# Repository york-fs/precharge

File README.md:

# Precharge Board

The precharge board is responsible for precharging the inverter's large capacitance through a dedicated relay and
resistor before the AIRs close.

[Latest Release](https://github.com/york-fs/precharge/releases/latest)
[Interactive BOM](https://york-fs.github.io/precharge/ibom.html)

## Features

* **CAN Communication**
* **AIR Relay Control**
* **HV Sampling of Accumulator and TS sides**

## Cloning

A recursive clone must be used to download the `kicad-library` repository:

    git clone --recursive https://github.com/york-fs/precharge.git

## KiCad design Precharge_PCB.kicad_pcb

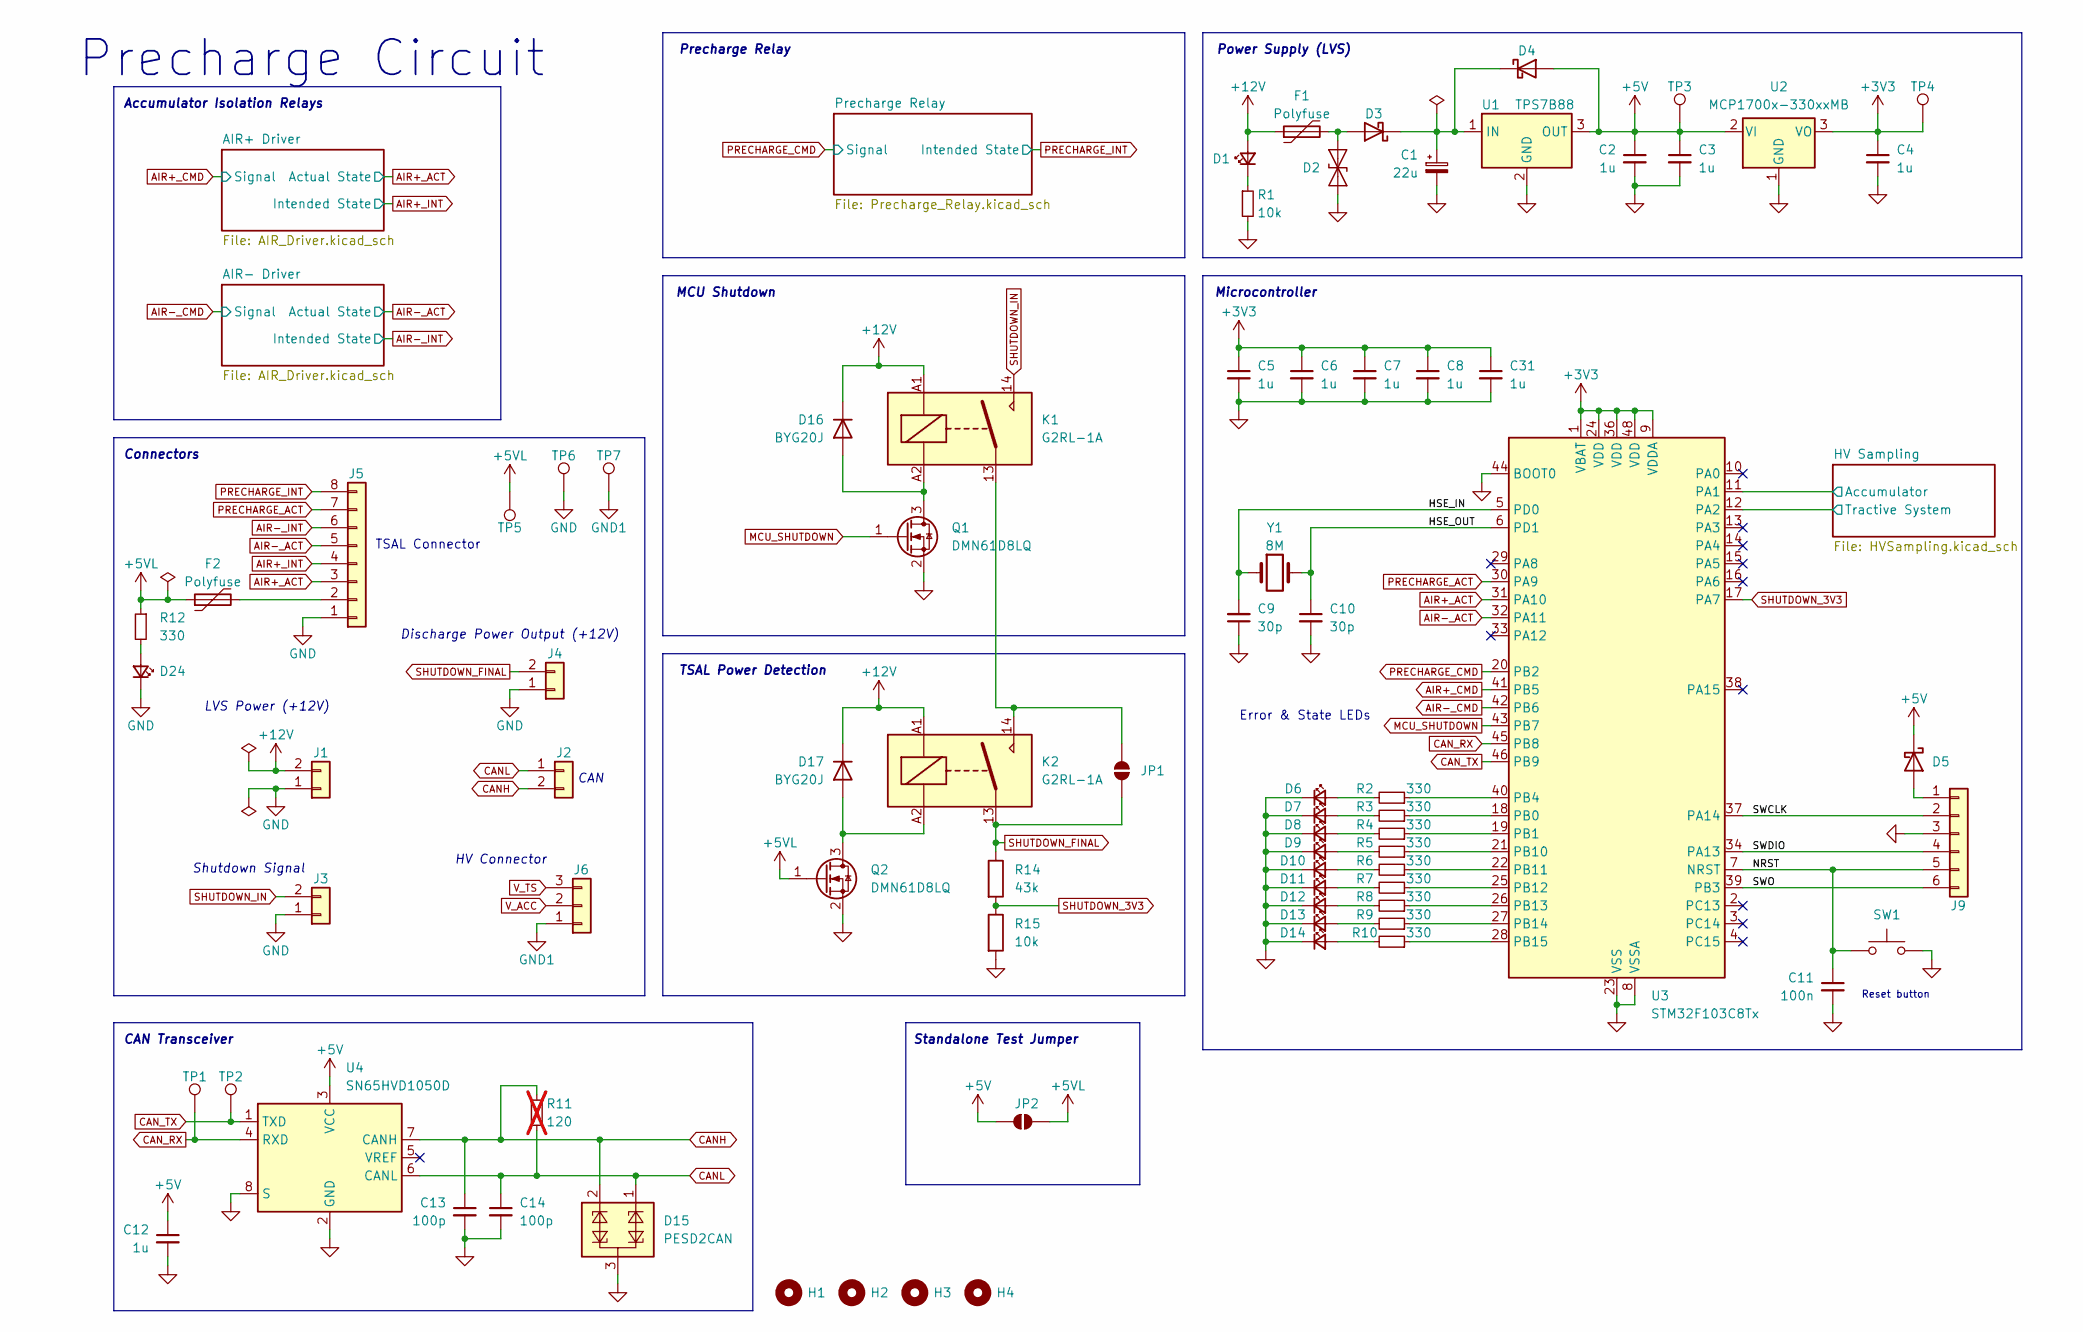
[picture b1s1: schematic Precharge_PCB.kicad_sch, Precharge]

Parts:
C1: 22u; CP_Elec_6.3x7.7; Mfr # EEEFK1J220XP; DigiKey # PCE3821CT-ND
C2, C3, C4, C5, C6, C7, C8, C12, C31: 1u; C_0603_1608Metric; Mfr # CL10B105KB8NQNC; LCSC # C5199872
C9, C10: 30p; C_0603_1608Metric; Mfr # GQM1875C2E300GB12D; DigiKey # 490-GQM1875C2E300GB12DCT-ND
C11: 100n; C_0603_1608Metric; Mfr # CL10B104KB8NNNC; DigiKey # 1276-1000-1-ND
C13, C14: 100p; C_0603_1608Metric; Mfr # GCM1885C2A101JA16D; DigiKey # 490-4771-1-ND
D1, D6, D7, D8, D9, D10, D11, D12, D13, D14, D24: LED_Small; LED_0603_1608Metric; Mfr # NCD0603R1; LCSC # C84263
D2: SMAJ24CA; D_SMA; Mfr # SMAJ24CA; DigiKey # SMAJ24CALFCT-ND
D3, D4, D5: D_Schottky; D_SOD-323; Mfr # NSR0530H; DigiKey # NSR0530HT1GOSCT-ND
D15: PESD2CAN; SOT-23; Mfr # PESD2CAN,215; DigiKey # 1727-3891-1-ND
D16, D17: BYG20J; D_SMA; Mfr # BYG20J-E3/TR; DigiKey # BYG20J-E3/TR3GICT-ND
F1, F2: Polyfuse; C_0805_2012Metric; Mfr # 0805L010/24YR; DigiKey # F11311CT-ND
H1, H2, H3, H4: MountingHole; MountingHole_3.2mm_M3
J1: Conn_01x02; MolexMicrofitPlus1x2; Mfr # 2157601022; DigiKey # 900-2157601022-ND
J2, J4: Conn_01x02; MolexMicrofitPlus1x2; Mfr # 2157601002; DigiKey # 900-2157601002-ND
J3: Conn_01x02; MolexMicrofitPlus1x2; Mfr # 2157601032; DigiKey # 900-2157601032-ND
J5: Conn_01x08; MolexMicrofitPlus1x8; Mfr # 2157601008; DigiKey # 900-2157601008-ND
J6: Conn_01x03; MolexMicrofitPlus1x3; Mfr # 2157601043; DigiKey # 900-2157601043-ND
J9: Conn_01x06; IDC-Connector-2x3; Mfr # HX JN1.27-2x3P ZZ H4.9; LCSC # C42372545
JP1, JP2: SolderJumper_2_Open; SolderJumper-2_P1.3mm_Open_TrianglePad1.0x1.5mm
K1, K2: G2RL-1A; Relay_SPST_Omron_G2RL-1A; Mfr # G2RL-1A-DC12; DigiKey # Z140-ND
Q1, Q2: DMN61D8LQ; SOT-23; Mfr # DMN61D8LQ-7; DigiKey # DMN61D8LQ-7DICT-ND
R1, R15: 10k; R_0603_1608Metric; Mfr # 0603WAF1002T5E; LCSC # C25804
R2, R3, R4, R5, R6, R7, R8, R9, R10, R12: 330; R_0603_1608Metric; Mfr # 0603WAF3300T5E; LCSC # C23138
R11: 120; R_0603_1608Metric; not fitted
R14: 43k; R_0603_1608Metric
SW1: SW_Push; SW_Push_1P1T_NO_Vertical_Wuerth_434133025816; Mfr # SKRPACE010; DigiKey # 4809-SKRPACE010CT-ND
TP1, TP2, TP3, TP4, TP5, TP6, TP7: TestPoint; TestPoint_Keystone_5000-5004_Miniature; Mouser # 534-5000; DigiKey # 36-5000-ND
U1: TPS7B88; TO-252-2; Mfr # TPS7B8850QKVURQ1; DigiKey # 296-TPS7B8850QKVURQ1CT-ND
U2: MCP1700x-330xxMB; SOT-89-3; Mfr # MCP1700T-3302E/MB; DigiKey # MCP1700T3302EMBCT-ND
U3: STM32F103C8Tx; LQFP-48_7x7mm_P0.5mm; Mfr # STM32F103C8T6; DigiKey # 497-17666-1-ND
U4: SN65HVD1050D; SOIC-8_3.9x4.9mm_P1.27mm; Mfr # SN65HVD1050DR; DigiKey # 296-26335-1-ND
Y1: 8M; Crystal_SMD_5032-2Pin_5.0x3.2mm; Mfr # X50328MSB2GI; LCSC # C115962

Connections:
+3V3: C4.1, C5.1, C6.1, C7.1, C8.1, C31.1, TP4.1, U2.3 (VO), U3.1 (VBAT), U3.9 (VDDA), U3.24 (VDD), U3.36 (VDD), U3.48 (VDD); also elsewhere on the board
+5V: C2.1, C3.1, C12.1, D4.2 (A), D5.1 (K), JP2.2 (B), TP3.1, U1.3 (OUT), U2.2 (VI), U4.3 (VCC)
+5VL: F2.1, JP2.1 (A), Q2.1 (G), R12.1, TP5.1; also elsewhere on the board
+12V: D1.2 (A), D16.1 (K), D17.1 (K), F1.1, J1.2, K1.A1, K2.A1
/HSE_IN: C9.2, U3.5 (PD0), Y1.1
/HSE_OUT: C10.1, U3.6 (PD1), Y1.2
/HV Sampling/Accumulator: U3.11 (PA1); also elsewhere on the board
/HV Sampling/Tractive System: U3.12 (PA2); also elsewhere on the board
/NRST: C11.1, J9.5, SW1.1, U3.7 (NRST)
/SWCLK: J9.2, U3.37 (PA14)
/SWDIO: J9.4, U3.34 (PA13)
/SWO: J9.6, U3.39 (PB3)
AIR+_ACT: J5.3, U3.31 (PA10); also elsewhere on the board
AIR+_CMD: U3.41 (PB5); also elsewhere on the board
AIR+_INT: J5.4; also elsewhere on the board
AIR-_ACT: J5.5, U3.32 (PA11); also elsewhere on the board
AIR-_CMD: U3.42 (PB6); also elsewhere on the board
AIR-_INT: J5.6; also elsewhere on the board
CANH: C13.1, D15.2 (C2), J2.2, R11.1, U4.7 (CANH)
CANL: C14.1, D15.1 (C1), J2.1, R11.2, U4.6 (CANL)
CAN_RX: TP1.1, U3.45 (PB8), U4.4 (RXD)
CAN_TX: TP2.1, U3.46 (PB9), U4.1 (TXD)
GND: C1.2, C2.2, C3.2, C4.2, C5.2, C6.2, C7.2, C8.2, C9.1, C10.2, C11.2, C12.2, C13.2, C14.2, C31.2, D2.1 (A1), D6.1 (K), D7.1 (K), D8.1 (K), D9.1 (K), D10.1 (K), D11.1 (K), D12.1 (K), D13.1 (K), D14.1 (K), D15.3 (CC), D24.1 (K), J1.1, J3.1, J4.1, J5.1, J9.3, Q1.2 (S), Q2.2 (S), R1.2, R15.2, SW1.2, TP6.1, U1.2 (GND), U2.1 (GND), U3.8 (VSSA), U3.23 (VSS), U3.35 (VSS), U3.44 (BOOT0), U3.47 (VSS), U4.2 (GND), U4.8 (S); also elsewhere on the board
GND1: J6.1, TP7.1; also elsewhere on the board
MCU_SHUTDOWN: Q1.1 (G), U3.43 (PB7)
unnamed: D1.1 (K), R1.1
unnamed: D2.2 (A2), D3.2 (A), F1.2
unnamed: C1.1, D3.1 (K), D4.1 (K), U1.1 (IN)
unnamed: D5.2 (A), J9.1
unnamed: D6.2 (A), R2.2
unnamed: D7.2 (A), R3.2
unnamed: D8.2 (A), R4.2
unnamed: D9.2 (A), R5.2
unnamed: D10.2 (A), R6.2
unnamed: D11.2 (A), R7.2
unnamed: D12.2 (A), R8.2
unnamed: D13.2 (A), R9.2
unnamed: D14.2 (A), R10.2
unnamed: D16.2 (A), K1.A2, Q1.3 (D)
unnamed: D17.2 (A), K2.A2, Q2.3 (D)
unnamed: D24.2 (A), R12.2
unnamed: F2.2, J5.2
unnamed: JP1.2 (B), K1.13, K2.14
unnamed: R3.1, U3.18 (PB0)
unnamed: R4.1, U3.19 (PB1)
unnamed: R2.1, U3.40 (PB4)
unnamed: R5.1, U3.21 (PB10)
unnamed: R6.1, U3.22 (PB11)
unnamed: R7.1, U3.25 (PB12)
unnamed: R8.1, U3.26 (PB13)
unnamed: R9.1, U3.27 (PB14)
unnamed: R10.1, U3.28 (PB15)
PRECHARGE_ACT: J5.7, U3.30 (PA9); also elsewhere on the board
PRECHARGE_CMD: U3.20 (PB2); also elsewhere on the board
PRECHARGE_INT: J5.8; also elsewhere on the board
SHUTDOWN_3V3: R14.2, R15.1, U3.17 (PA7)
SHUTDOWN_FINAL: J4.2, JP1.1 (A), K2.13, R14.1; also elsewhere on the board
SHUTDOWN_IN: J3.2, K1.14
V_ACC: J6.2; also elsewhere on the board
V_TS: J6.3; also elsewhere on the board

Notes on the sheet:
Microcontroller
Error & State LEDs
Connectors
Accumulator Isolation Relays
Standalone Test Jumper
TSAL Power Detection
CAN Transceiver
HV Connector
Power Supply (LVS)
Shutdown Signal
TSAL Connector
Precharge Relay
CAN
Discharge Power Output (+12V)
LVS Power (+12V)
Reset button
MCU Shutdown
Precharge Circuit

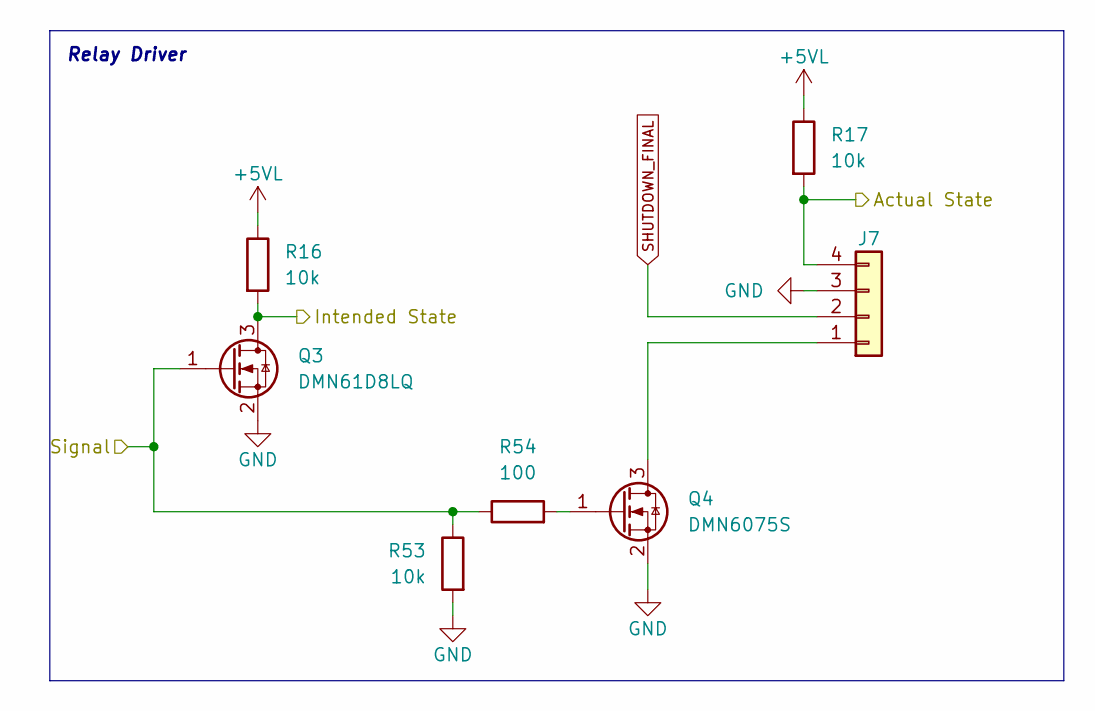
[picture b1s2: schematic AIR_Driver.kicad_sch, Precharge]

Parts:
J7: Conn_01x04; MolexMicrofitPlus1x4; Mfr # 2157601004; DigiKey # 900-2157601004-ND
Q3: DMN61D8LQ; SOT-23; Mfr # DMN61D8LQ-7; DigiKey # DMN61D8LQ-7DICT-ND
Q4: DMN6075S; SOT-23; Mfr # DMN6075S-7; DigiKey # DMN6075S-7DICT-ND
R16, R17, R53: 10k; R_0603_1608Metric; Mfr # 0603WAF1002T5E; LCSC # C25804
R54: 100; R_0603_1608Metric

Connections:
+5VL: R16.1, R17.1; also elsewhere on the board
AIR+_ACT: J7.4, R17.2; also elsewhere on the board
AIR+_CMD: Q3.1 (G), R53.1, R54.1; also elsewhere on the board
AIR+_INT: Q3.3 (D), R16.2; also elsewhere on the board
GND: J7.3, Q3.2 (S), Q4.2 (S), R53.2; also elsewhere on the board
unnamed: J7.1, Q4.3 (D)
unnamed: Q4.1 (G), R54.2
SHUTDOWN_FINAL: J7.2; also elsewhere on the board

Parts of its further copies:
J8: Conn_01x04; MolexMicrofitPlus1x4; Mfr # 2157601004; DigiKey # 900-2157601004-ND
Q5: DMN61D8LQ; SOT-23; Mfr # DMN61D8LQ-7; DigiKey # DMN61D8LQ-7DICT-ND
Q6: DMN6075S; SOT-23; Mfr # DMN6075S-7; DigiKey # DMN6075S-7DICT-ND
R18, R19, R55: 10k; R_0603_1608Metric; Mfr # 0603WAF1002T5E; LCSC # C25804
R56: 100; R_0603_1608Metric

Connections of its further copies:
+5VL: R18.1, R19.1; also elsewhere on the board
AIR-_ACT: J8.4, R19.2; also elsewhere on the board
AIR-_CMD: Q5.1 (G), R55.1, R56.1; also elsewhere on the board
AIR-_INT: Q5.3 (D), R18.2; also elsewhere on the board
GND: J8.3, Q5.2 (S), Q6.2 (S), R55.2; also elsewhere on the board
unnamed: J8.1, Q6.3 (D)
unnamed: Q6.1 (G), R56.2
SHUTDOWN_FINAL: J8.2; also elsewhere on the board

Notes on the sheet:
Relay Driver

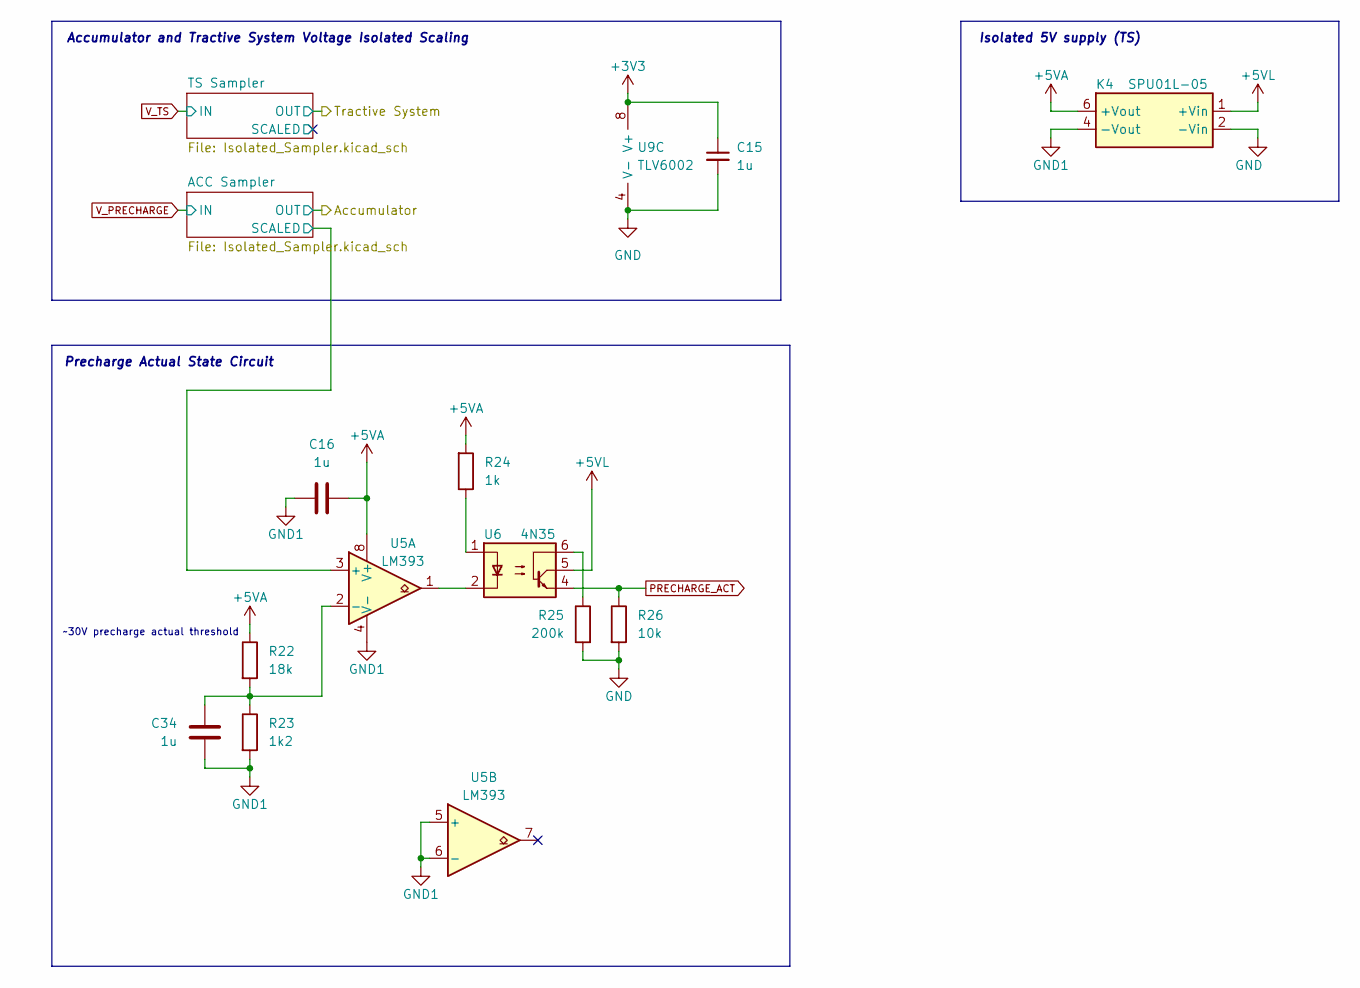
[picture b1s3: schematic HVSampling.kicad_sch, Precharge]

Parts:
C15, C16, C34: 1u; C_0603_1608Metric; Mfr # CL10B105KB8NQNC; LCSC # C5199872
K4: SPU01L-05; SPU01M-5; Mfr # SPU01L-05; DigiKey # 1866-4835-ND
R22: 18k; R_0603_1608Metric
R23: 1k2; R_0603_1608Metric
R24: 1k; R_0603_1608Metric; Mfr # 0603WAF1001T5E; LCSC # C21190
R25: 200k; R_0603_1608Metric
R26: 10k; R_0603_1608Metric; Mfr # 0603WAF1002T5E; LCSC # C25804
U5: LM393; SOIC-8_3.9x4.9mm_P1.27mm; Mfr # LM393DR; DigiKey # 296-1015-1-ND
U6: 4N35; DIP-6_W7.62mm; Mfr # 4N35M; DigiKey # 4N35MFS-ND
U9: TLV6002; SOIC-8_3.9x4.9mm_P1.27mm; Mfr # TLV6002QDRQ1; DigiKey # 296-TLV6002QDRQ1CT-ND

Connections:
+3V3: C15.1, U9.8 (V+); also elsewhere on the board
+5VA: C16.2, K4.6 (+Vout), R22.1, R24.2, U5.8 (V+); also elsewhere on the board
+5VL: K4.1 (+Vin), U6.5; also elsewhere on the board
/HV Sampling/ACC Sampler/SCALED: U5.3 (+); also elsewhere on the board
/HV Sampling/Tractive System: U9.7; also elsewhere on the board
GND: C15.2, K4.2 (-Vin), R25.2, R26.2, U9.4 (V-); also elsewhere on the board
GND1: C16.1, C34.1, K4.4 (-Vout), R23.2, U5.4 (V-), U5.5 (+), U5.6 (-); also elsewhere on the board
unnamed: R24.1, U6.1
unnamed: R25.1, U6.6
unnamed: U5.1, U6.2
unnamed: C34.2, R22.2, R23.1, U5.2 (-)
unnamed 84: U9.5 (+); also elsewhere on the board
unnamed 85: U9.6 (-); also elsewhere on the board
PRECHARGE_ACT: R26.1, U6.4; also elsewhere on the board

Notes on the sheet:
~30V precharge actual threshold
Precharge Actual State Circuit
Isolated 5V supply (TS)
Accumulator and Tractive System Voltage Isolated Scaling

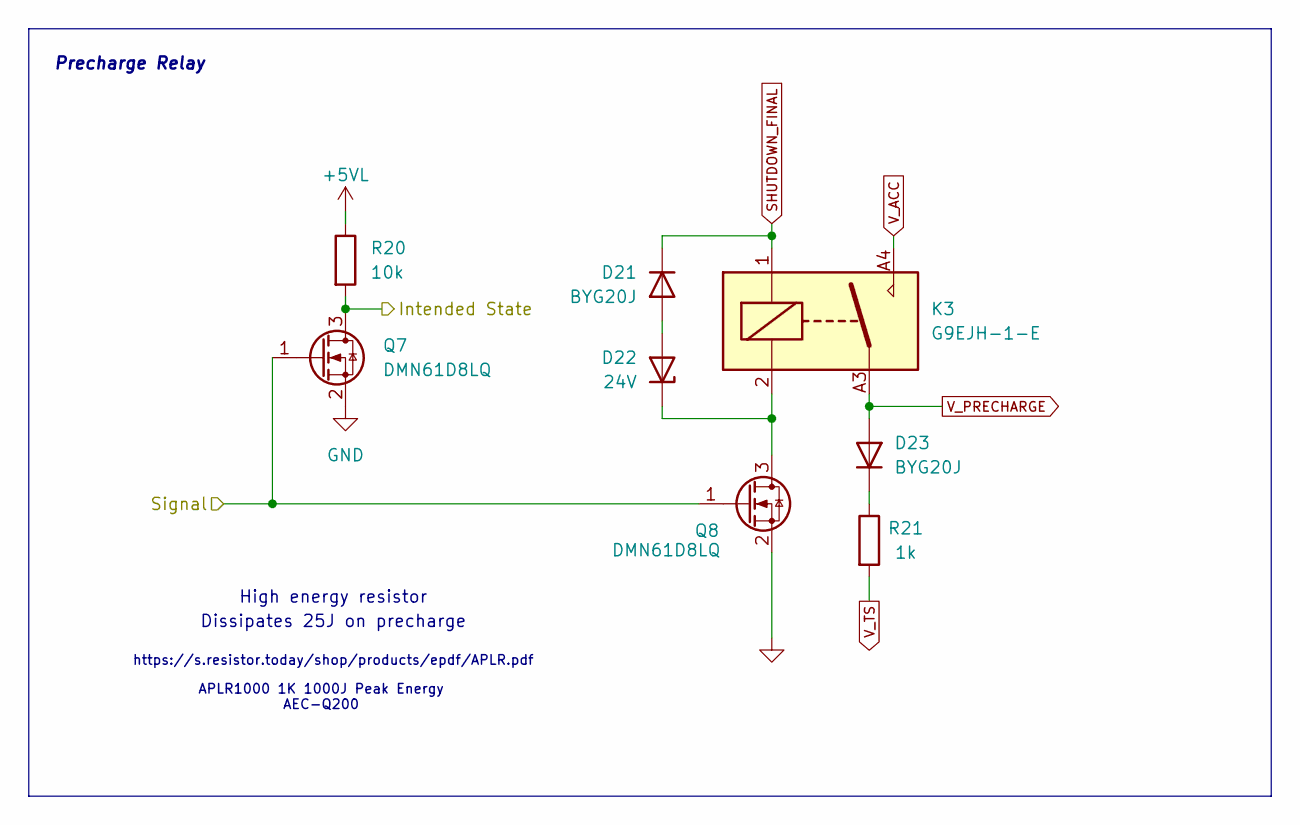
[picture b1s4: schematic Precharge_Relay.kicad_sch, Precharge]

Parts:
D21, D23: BYG20J; D_SMA; Mfr # BYG20J-E3/TR; DigiKey # BYG20J-E3/TR3GICT-ND
D22: 24V; D_SMA; Mfr # BZG05C24-M3-08; DigiKey # BZG05C24-M3-08GICT-ND
K3: G9EJH-1-E; Mfr # G9EJH-1-P-E DC12; DigiKey # 39-G9EJH-1-P-EDC12-ND
Q7, Q8: DMN61D8LQ; SOT-23; Mfr # DMN61D8LQ-7; DigiKey # DMN61D8LQ-7DICT-ND
R20: 10k; R_0603_1608Metric; Mfr # 0603WAF1002T5E; LCSC # C25804
R21: 1k; APLR1000; Mfr # APLR1000J1K00SE; DigiKey # 4506-APLR1000J1K00SE-ND

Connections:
+5VL: R20.1; also elsewhere on the board
GND: Q7.2 (S), Q8.2 (S); also elsewhere on the board
unnamed: D21.2 (A), D22.2 (A)
unnamed: D22.1 (K), K3.2, Q8.3 (D)
unnamed: D23.1 (K), R21.1
PRECHARGE_CMD: Q7.1 (G), Q8.1 (G); also elsewhere on the board
PRECHARGE_INT: Q7.3 (D), R20.2; also elsewhere on the board
SHUTDOWN_FINAL: D21.1 (K), K3.1; also elsewhere on the board
V_ACC: K3.A4, K3.B4; also elsewhere on the board
V_PRECHARGE: D23.2 (A), K3.A3, K3.B3; also elsewhere on the board
V_TS: R21.2; also elsewhere on the board

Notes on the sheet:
APLR1000 1K 1000J Peak Energy AEC-Q200
https://s.resistor.today/shop/products/epdf/APLR.pdf
Dissipates 25J on precharge
High energy resistor
Precharge Relay

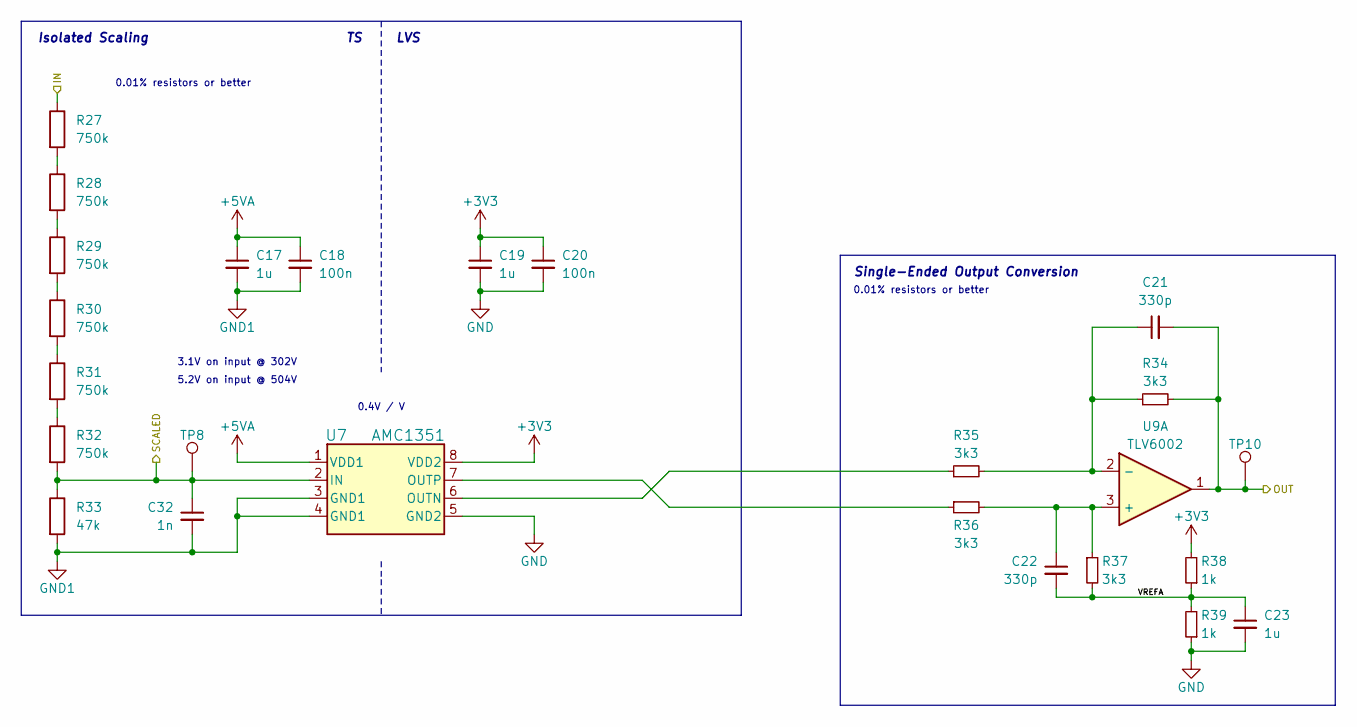
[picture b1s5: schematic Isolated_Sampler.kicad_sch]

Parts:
C17, C19, C23: 1u; C_0603_1608Metric; Mfr # CL10B105KB8NQNC; LCSC # C5199872
C18, C20: 100n; C_0603_1608Metric; Mfr # CL10B104KB8NNNC; DigiKey # 1276-1000-1-ND
C21, C22: 330p; C_0603_1608Metric; Mouser # 81-GCM1885C2A331J16D; DigiKey # 490-4948-1-ND
C32: 1n; C_0603_1608Metric; Mouser # 81-GRM39C102J50; DigiKey # 490-1451-1-ND
R27, R28, R29, R30, R31, R32: 750k; R_1206_3216Metric
R33: 47k; R_1206_3216Metric
R34, R35, R36, R37: 3k3; R_0603_1608Metric
R38, R39: 1k; R_0603_1608Metric; Mfr # 0603WAF1001T5E; LCSC # C21190
TP8, TP10: TestPoint; TestPoint_Keystone_5000-5004_Miniature; Mouser # 534-5000; DigiKey # 36-5000-ND
U7: AMC1351; SOIC-8_7.5x5.85mm_P1.27mm; Mfr # AMC1351QDWVRQ1; DigiKey # 296-AMC1351QDWVRQ1CT-ND
U9: TLV6002; SOIC-8_3.9x4.9mm_P1.27mm; Mfr # TLV6002QDRQ1; DigiKey # 296-TLV6002QDRQ1CT-ND

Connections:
+3V3: C19.1, C20.1, R38.2, U7.8 (VDD2); also elsewhere on the board
+5VA: C17.1, C18.1, U7.1 (VDD1); also elsewhere on the board
/HV Sampling/ACC Sampler/SCALED: C32.1, R32.2, R33.1, TP8.1, U7.2 (IN); also elsewhere on the board
/HV Sampling/ACC Sampler/VREFA: C22.2, C23.1, R37.2, R38.1, R39.2
/HV Sampling/Accumulator: C21.2, R34.2, TP10.1, U9.1; also elsewhere on the board
/HV Sampling/Tractive System: U9.7; also elsewhere on the board
GND: C19.2, C20.2, C23.2, R39.1, U7.5 (GND2); also elsewhere on the board
GND1: C17.2, C18.2, C32.2, R33.2, U7.3 (GND1), U7.4 (GND1); also elsewhere on the board
unnamed: R27.2, R28.1
unnamed: R28.2, R29.1
unnamed: R29.2, R30.1
unnamed: R30.2, R31.1
unnamed: R31.2, R32.1
unnamed: R35.1, U7.6 (OUTN)
unnamed: R36.1, U7.7 (OUTP)
unnamed: C22.1, R36.2, R37.1, U9.3 (+)
unnamed: C21.1, R34.1, R35.2, U9.2 (-)
unnamed 84: U9.5 (+); also elsewhere on the board
unnamed 85: U9.6 (-); also elsewhere on the board
V_PRECHARGE: R27.1; also elsewhere on the board

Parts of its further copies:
C24, C26, C30: 1u; C_0603_1608Metric; Mfr # CL10B105KB8NQNC; LCSC # C5199872
C25, C27: 100n; C_0603_1608Metric; Mfr # CL10B104KB8NNNC; DigiKey # 1276-1000-1-ND
C28, C29: 330p; C_0603_1608Metric; Mouser # 81-GCM1885C2A331J16D; DigiKey # 490-4948-1-ND
C33: 1n; C_0603_1608Metric; Mouser # 81-GRM39C102J50; DigiKey # 490-1451-1-ND
R40, R41, R42, R43, R44, R45: 750k; R_1206_3216Metric
R46: 47k; R_1206_3216Metric
R47, R48, R49, R50: 3k3; R_0603_1608Metric
R51, R52: 1k; R_0603_1608Metric; Mfr # 0603WAF1001T5E; LCSC # C21190
TP9, TP11: TestPoint; TestPoint_Keystone_5000-5004_Miniature; Mouser # 534-5000; DigiKey # 36-5000-ND
U8: AMC1351; SOIC-8_7.5x5.85mm_P1.27mm; Mfr # AMC1351QDWVRQ1; DigiKey # 296-AMC1351QDWVRQ1CT-ND

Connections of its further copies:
+3V3: C26.1, C27.1, R51.2, U8.8 (VDD2); also elsewhere on the board
+5VA: C24.1, C25.1, U8.1 (VDD1); also elsewhere on the board
/HV Sampling/TS Sampler/SCALED: C33.1, R45.2, R46.1, TP9.1, U8.2 (IN)
/HV Sampling/TS Sampler/VREFA: C29.2, C30.1, R50.2, R51.1, R52.2
/HV Sampling/Tractive System: C28.2, R47.2, TP11.1; also elsewhere on the board
GND: C26.2, C27.2, C30.2, R52.1, U8.5 (GND2); also elsewhere on the board
GND1: C24.2, C25.2, C33.2, R46.2, U8.3 (GND1), U8.4 (GND1); also elsewhere on the board
unnamed: R40.2, R41.1
unnamed: R41.2, R42.1
unnamed: R42.2, R43.1
unnamed: R43.2, R44.1
unnamed: R44.2, R45.1
unnamed: R48.1, U8.6 (OUTN)
unnamed: R49.1, U8.7 (OUTP)
unnamed 84: C29.1, R49.2, R50.1; also elsewhere on the board
unnamed 85: C28.1, R47.1, R48.2; also elsewhere on the board
V_TS: R40.1; also elsewhere on the board

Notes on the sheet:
3.1V on input @ 302V
0.01% resistors or better
Single-Ended Output Conversion
0.4V / V
5.2V on input @ 504V
Isolated Scaling
LVS

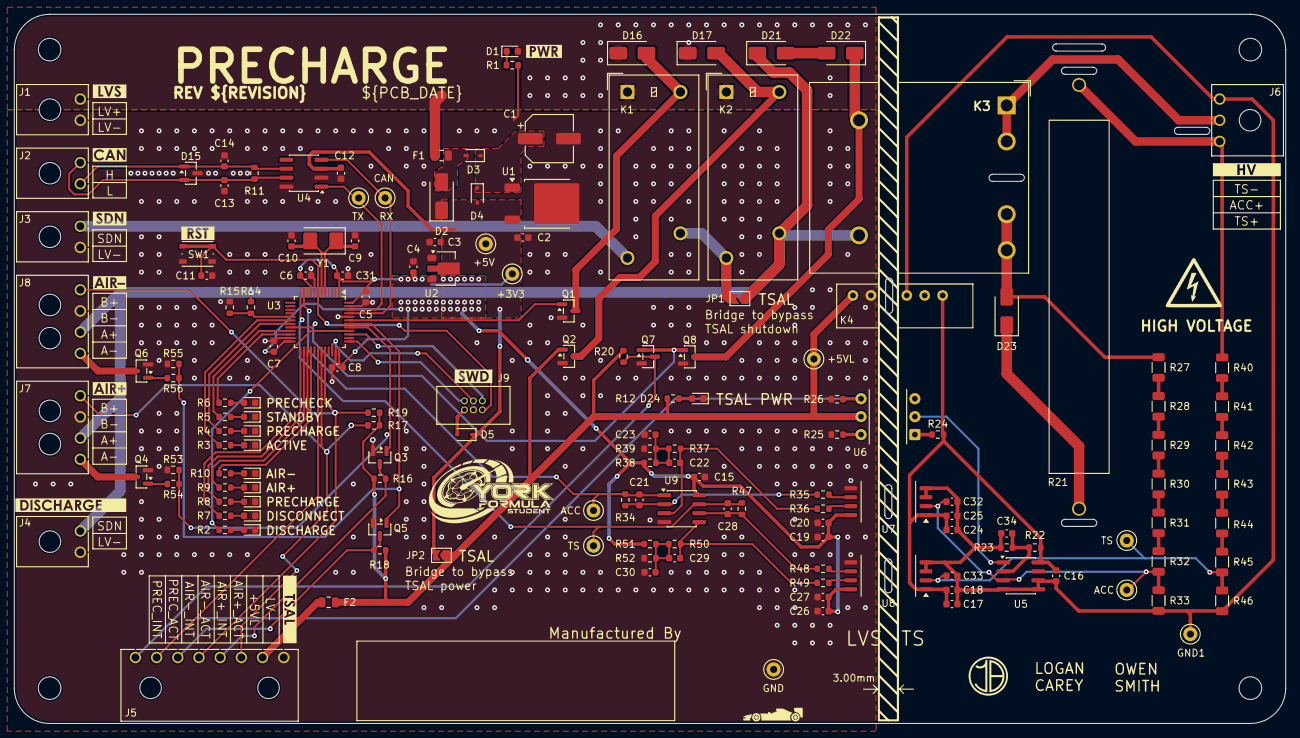
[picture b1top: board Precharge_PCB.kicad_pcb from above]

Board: 2 copper layers, 180.0 x 100.4 mm, 172 parts (0 on the bottom side), 95 nets.

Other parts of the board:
kibuzzard-6910BB45: G***; kibuzzard-6910BB45
kibuzzard-6910BB76: G***; kibuzzard-6910BB76
kibuzzard-694056F2: G***; kibuzzard-694056F2
kibuzzard-694056F9: G***; kibuzzard-694056F9
kibuzzard-694058AC: G***; kibuzzard-694058AC
kibuzzard-694058D8: G***; kibuzzard-694058D8
kibuzzard-6940937D: G***; kibuzzard-6940937D
kibuzzard-69405726: G***; kibuzzard-69405726
kibuzzard-69405880: G***; kibuzzard-69405880
kibuzzard-69405918: G***; kibuzzard-69405918
kibuzzard-69408760: G***; kibuzzard-69408760

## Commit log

2025-11-19 pcb: Create blank PCB
2025-11-19 schematic: Remove unused EEPROM pins on MCU
2025-11-19 schematic: Connect MCU shutdown pin
2025-11-19 schematic: Change incorrect 3.3V net to 3V3
2025-11-19 schematic: Fix incorrect net on precharge relay
2025-11-19 *: Add a variable for the revision
2025-11-19 schematic: Add a CAN connector
2025-11-22 meta: Update gitignore
2025-11-23 meta: Create a README
2025-11-23 ci: Add kicad workflow
2025-11-23 meta: Add kicad-library submodule
2025-12-09 Updated to single pole relay, removed relay drivers
2025-12-13 schematic: Switch to NSR0530H from SS34
2025-12-13 schematic: Switch to new push button
2025-12-13 schematic: Switch to new IDC SWD header
2025-12-13 schematic: Avoid using PA0 for analog sampling
2025-12-13 schematic: Cleanup all global labels
2025-12-13 schematic: Rename hierarchical sheets
2025-12-13 schematic: Remove old hierarchical sheets
2025-12-13 schematic: Update some symbols
2025-12-13 project: Add yfs symbol library
2025-12-13 schematic: Do some general tidying
2025-12-13 schematic: Adjust MCU shutdown sampling divider ratio
2025-12-13 schematic: Use SOD-323 zener diode
2025-12-13 schematic: Fix unconnected wires
2025-12-13 schematic: Add a pull-down to the TSAL power detection MOSFET
2025-12-13 schematic: Mark AIR flyback diodes as DNP
    The contactors should have them built-in.
2025-12-13 project: Add yfs footprint library
2025-12-13 project: Set BOM options
2025-12-13 schematic: Update molex connectors
2025-12-13 kicad-library: Update to latest version
2025-12-13 *: Use kicad-library exclusively
2025-12-13 *: Delete old component libraries
2025-12-13 schematic: Tie unused LM393 inputs low
2025-12-13 schematic: Connect relay actual states to the MCU
2025-12-13 schematic: Add a TVS diode to the LVS input
2025-12-13 schematic: Create a hierarchical sheet for the isolated amplifiers
2025-12-13 schematic: Add a 200k pull-down to the 4N35 base
2025-12-13 schematic: Renumber hierarchical pages
2025-12-13 schematic: Assign all footprints
2025-12-13 schematic: Power precharge relay from shutdown
2025-12-13 schematic: Reassign reference designators
2025-12-13 schematic: Fill out most of the BOM
2025-12-14 pcb: Setup net classes and import components
2025-12-14 pcb: Add a HV net class
2025-12-17 Revision A
2025-12-25 *: Remove unnecessary MOSFET pull-downs
2025-12-25 schematic: Add zener diode across precharge relay
2025-12-26 Updated layout
2025-12-26 Tidied up board
2025-12-31 *: Add +5V to +5VL jumper
    This allows standalone precharge testing.
2025-12-31 pcb: Fix R21 designator orientation
2026-01-03 Added TSAL power bypass jumper
2026-01-03 Increased thermal relief spoke thickness
2026-02-02 schematic: Fix BOM for SPU01L-05 DC-DC converter
2026-02-02 schematic: Add BOM entries for precharge relay and associated zener
2026-02-03 *: Remove AIR flyback diodes
2026-02-03 schematic: Group all STM LEDs together
2026-02-03 *: Add test points around sampling
2026-02-03 pcb: Update kicad library footprints
2026-02-04 *: Add filter capacitors on HV sense inputs
2026-02-04 *: Change single-ended conversion bias resistors from 10k to 1k
2026-02-04 *: Fix AMC1351 footprint
2026-02-04 *: Set precharge comparator threshold resistors and add capacitor
2026-04-17 schematic: Fix shutdown net direction on some labels
2026-04-22 *: Measure shutdown voltage with STM ADC
2026-04-22 bom: Switch from 1N4007 to BYG20J
2026-04-22 *: Switch to new AIR driving MOSFETs
2026-04-22 *: Bump revision and date for revision B
2026-05-05 pcb: Add paste layers
2026-05-06 schematic: Update BOM
2026-06-28 pcb: Update model path for precharge relay
2026-06-28 meta: Update README
2026-06-28 pcb: Update KiCad built-in library
2026-06-28 ci: Update to latest KiCad workflow
